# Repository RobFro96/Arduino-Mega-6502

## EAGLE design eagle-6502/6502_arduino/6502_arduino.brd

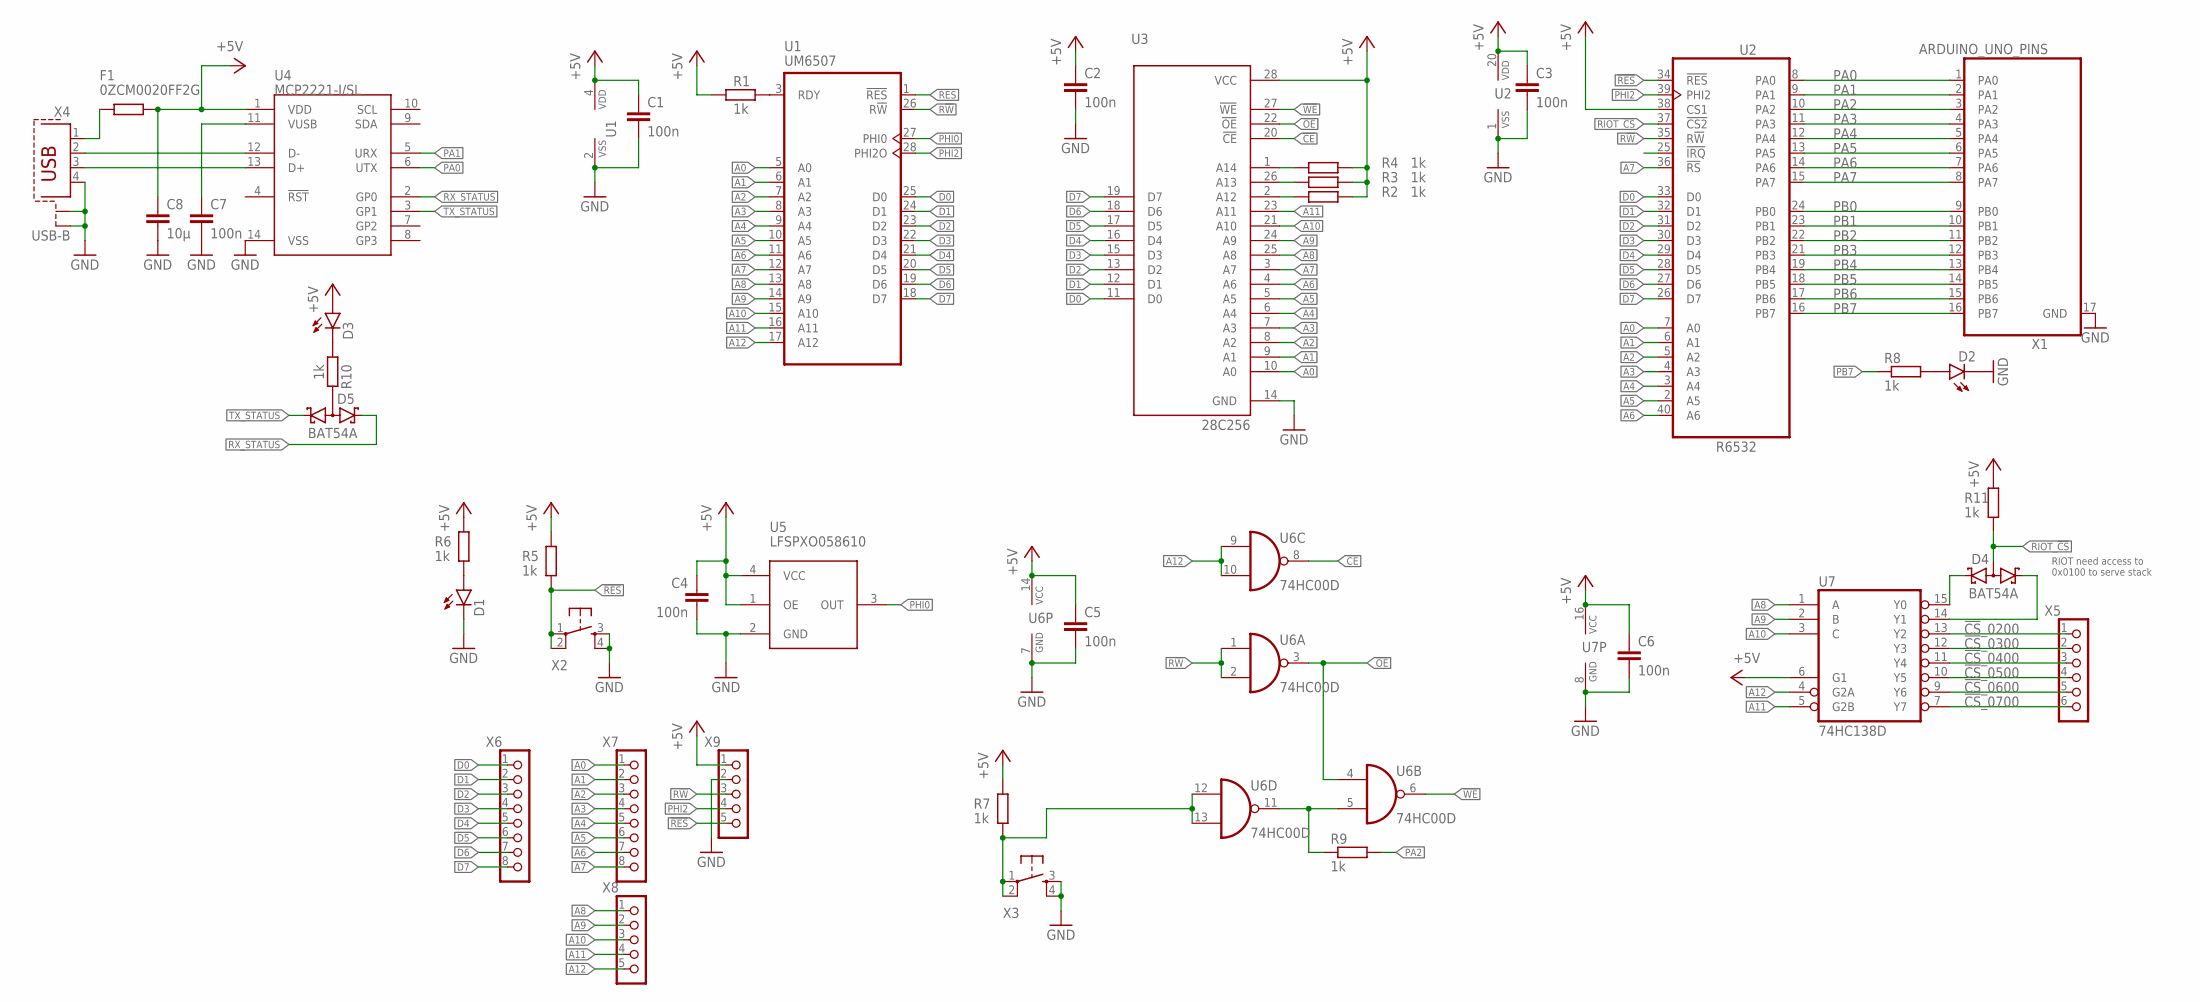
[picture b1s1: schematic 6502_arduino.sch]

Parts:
C1, C2, C3, C4, C5, C6, C7: 100n; C0805
C8: 10µ; C0805
D1, D2, D3: LED; LED3MM
D4, D5: BAT54A; SOT23
F1: 0ZCM0020FF2G; R0603
R1, R2, R3, R4, R5, R6, R7, R8, R9, R10, R11: 1k; R0805
U1: UM6507; DIL28-6
U2: R6532; DIL40
U3: 28C256; DIL28-6
U4: MCP2221-I/SL; SOIC14
U5: LFSPXO058610
U6: 74HC00D; SO14
U7: 74HC138D; SO16
X1: ARDUINO_UNO_PINS; ARDUINO_R3
X2, X3: TACT_SWITCH; TACTILE_SWITCH_PTH_6.0MM
X4: USB-B; PN61729-S
X5: PINHD_6_RND; 1X06
X6, X7: PINHD_8_RND; 1X08
X8, X9: PINHD_5_RND; 1X05

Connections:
!BOOT: R7.1, U6.12 (I0), U6.13 (I1), X3.1, X3.2
!CE: U3.20 (!CE), U6.8 (O)
!CS!_0200: U7.13 (Y2), X5.1
!CS!_0300: U7.12 (Y3), X5.2
!CS!_0400: U7.11 (Y4), X5.3
!CS!_0500: U7.10 (Y5), X5.4
!CS!_0600: U7.9 (Y6), X5.5
!CS!_0700: U7.7 (Y7), X5.6
!OE: U3.22 (!OE), U6.3 (O), U6.4 (I0)
!RES: R5.1, U1.1 (!RES), U2.34 (!RES), X2.1, X2.2, X9.5
!WE: U3.27 (!WE), U6.6 (O)
+5V: C1.1, C2.1, C3.1, C4.1, C5.1, C6.1, C8.1, D3.A, F1.2, R1.1, R2.2, R3.2, R4.2, R5.2, R6.2, R7.2, R11.2, U1.4 (VDD), U2.20 (VDD), U2.38 (CS1), U3.28 (VCC), U4.1 (VDD), U5.1 (OE), U5.4 (VCC), U6.14 (VCC), U7.6 (G1), U7.16 (VCC), X9.1
A0: U1.5 (A0), U2.7 (A0), U3.10 (A0), X7.1
A1: U1.6 (A1), U2.6 (A1), U3.9 (A1), X7.2
A2: U1.7 (A2), U2.5 (A2), U3.8 (A2), X7.3
A3: U1.8 (A3), U2.4 (A3), U3.7 (A3), X7.4
A4: U1.9 (A4), U2.3 (A4), U3.6 (A4), X7.5
A5: U1.10 (A5), U2.2 (A5), U3.5 (A5), X7.6
A6: U1.11 (A6), U2.40 (A6), U3.4 (A6), X7.7
A7: U1.12 (A7), U2.36 (!RS), U3.3 (A7), X7.8
A8: U1.13 (A8), U3.25 (A8), U7.1 (A), X8.1
A9: U1.14 (A9), U3.24 (A9), U7.2 (B), X8.2
A10: U1.15 (A10), U3.21 (A10), U7.3 (C), X8.3
A11: U1.16 (A11), U3.23 (A11), U7.5 (G2B), X8.4
A12: U1.17 (A12), U6.9 (I0), U6.10 (I1), U7.4 (G2A), X8.5
D0: U1.25 (D0), U2.33 (D0), U3.11 (D0), X6.1
D1: U1.24 (D1), U2.32 (D1), U3.12 (D1), X6.2
D2: U1.23 (D2), U2.31 (D2), U3.13 (D2), X6.3
D3: U1.22 (D3), U2.30 (D3), U3.15 (D3), X6.4
D4: U1.21 (D4), U2.29 (D4), U3.16 (D4), X6.5
D5: U1.20 (D5), U2.28 (D5), U3.17 (D5), X6.6
D6: U1.19 (D6), U2.27 (D6), U3.18 (D6), X6.7
D7: U1.18 (D7), U2.26 (D7), U3.19 (D7), X6.8
GND: C1.2, C2.2, C3.2, C4.2, C5.2, C6.2, C7.2, C8.2, D1.K (C), D2.K (C), U1.2 (VSS), U2.1 (VSS), U3.14 (GND), U4.14 (VSS), U5.2 (GND), U6.7 (GND), U7.8 (GND), X1.17 (GND), X2.3, X2.4, X3.3, X3.4, X4.4, X4.S1, X4.S2, X9.2
unnamed: R1.2, U1.3 (RDY)
unnamed: D1.A, R6.1
unnamed: R9.1, U6.5 (I1), U6.11 (O)
unnamed: D2.A, R8.2
unnamed: U4.12 (D-), X4.2
unnamed: U4.13 (D+), X4.3
unnamed: D3.K (C), R10.1
unnamed: C7.1, U4.11 (VUSB)
unnamed: D5.3 (AA), R10.2
unnamed: F1.1, X4.1
unnamed: D4.1 (K1), U7.15 (Y0)
unnamed: R2.1, U3.2 (A12)
unnamed: R3.1, U3.26 (A13)
unnamed: R4.1, U3.1 (A14)
unnamed: D4.2 (K2), U7.14 (Y1)
PA0: U2.8 (PA0), U4.6 (UTX), X1.1 (PA0)
PA1: U2.9 (PA1), U4.5 (URX), X1.2 (PA1)
PA2: R9.2, U2.10 (PA2), X1.3 (PA2)
PA3: U2.11 (PA3), X1.4 (PA3)
PA4: U2.12 (PA4), X1.5 (PA4)
PA5: U2.13 (PA5), X1.6 (PA5)
PA6: U2.14 (PA6), X1.7 (PA6)
PA7: U2.15 (PA7), X1.8 (PA7)
PB0: U2.24 (PB0), X1.9 (PB0)
PB1: U2.23 (PB1), X1.10 (PB1)
PB2: U2.22 (PB2), X1.11 (PB2)
PB3: U2.21 (PB3), X1.12 (PB3)
PB4: U2.19 (PB4), X1.13 (PB4)
PB5: U2.18 (PB5), X1.14 (PB5)
PB6: U2.17 (PB6), X1.15 (PB6)
PB7: R8.1, U2.16 (PB7), X1.16 (PB7)
PHI0: U1.27 (PHI0), U5.3 (OUT)
PHI2: U1.28 (PHI2O), U2.39 (PHI2), X9.4
R!W: U1.26 (R!W), U2.35 (R!W), U6.1 (I0), U6.2 (I1), X9.3
RIOT_!CS: D4.3 (AA), R11.1, U2.37 (!CS2)
RX_STATUS: D5.2 (K2), U4.2 (GP0)
TX_STATUS: D5.1 (K1), U4.3 (GP1)

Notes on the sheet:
RIOT need access to 0x0100 to serve stack

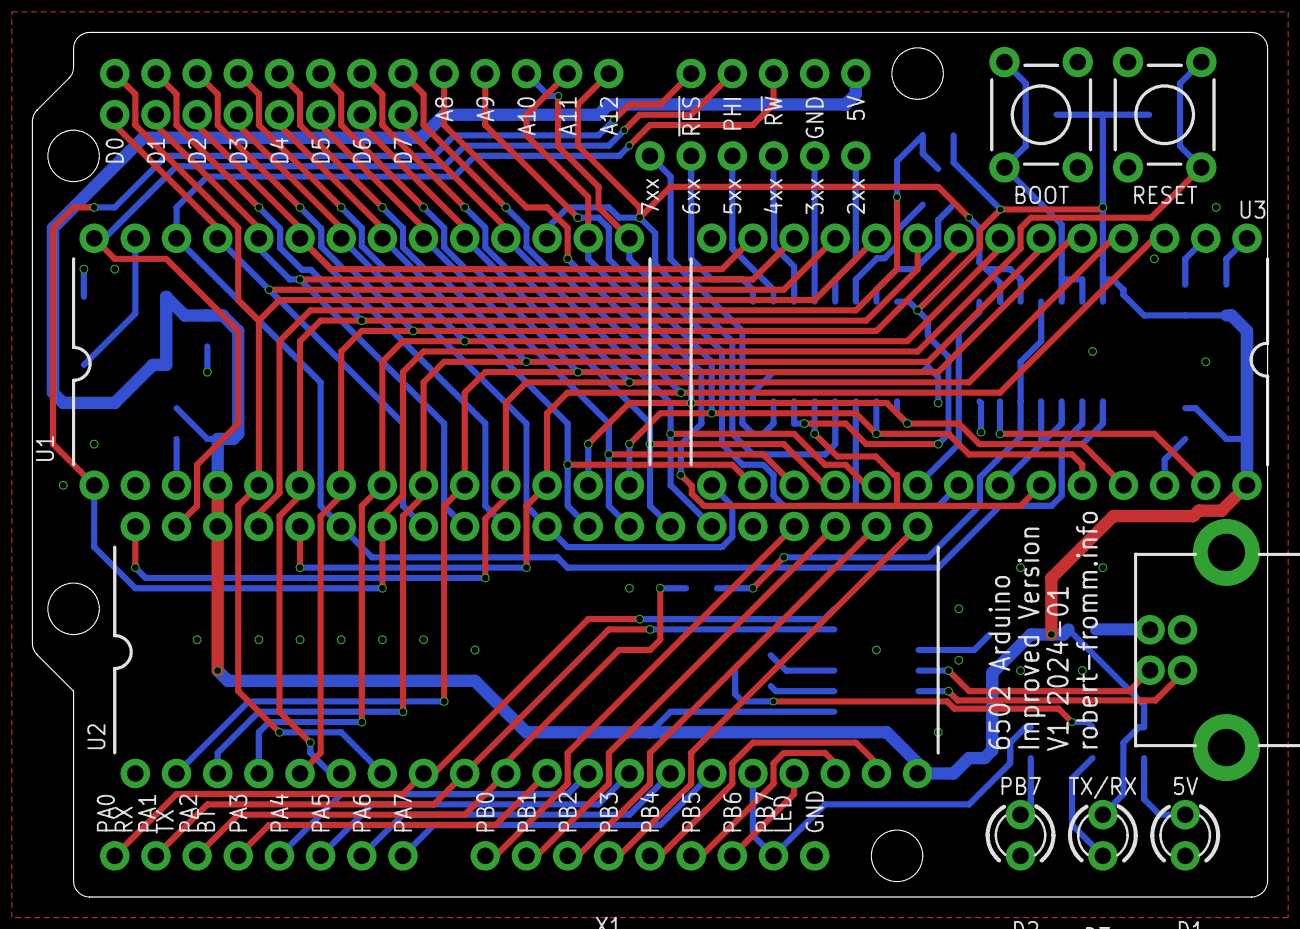
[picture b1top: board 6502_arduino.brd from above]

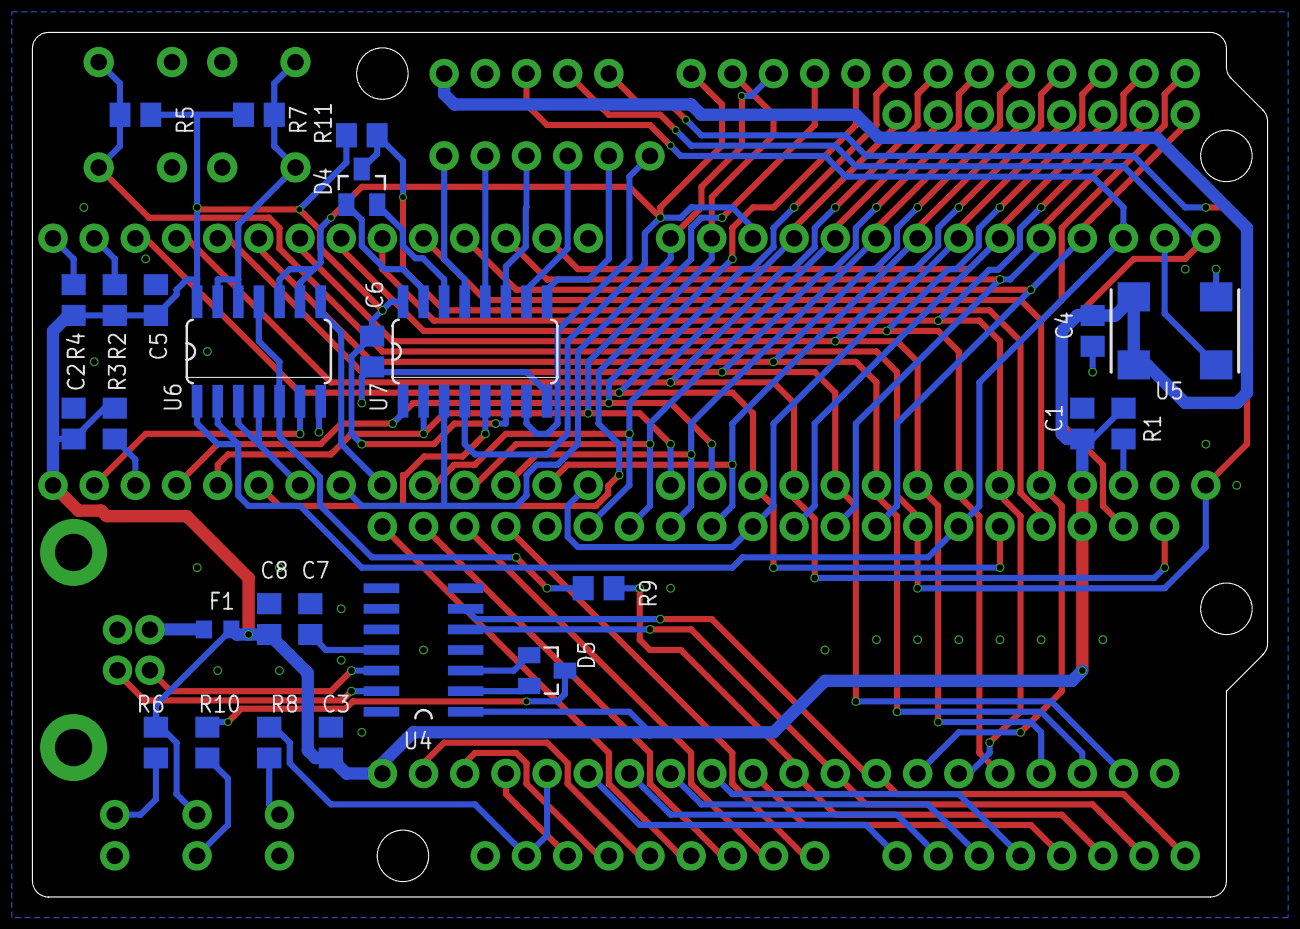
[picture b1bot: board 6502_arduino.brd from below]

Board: 2 copper layers, 76.2 x 53.3 mm, 41 parts (26 on the bottom side), 71 nets.

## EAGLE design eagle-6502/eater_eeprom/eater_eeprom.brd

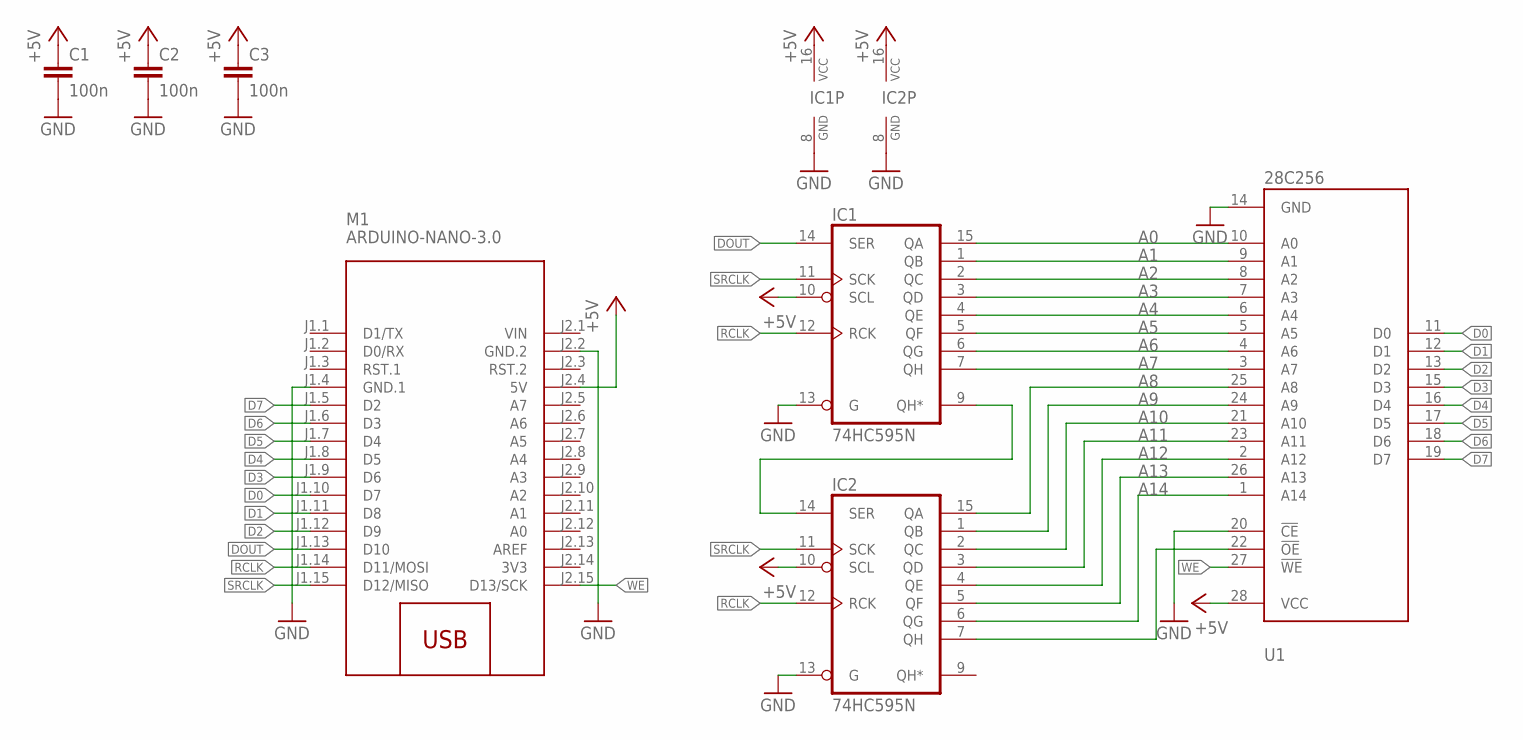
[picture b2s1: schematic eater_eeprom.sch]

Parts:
C1, C2, C3: 100n; C0805
IC1, IC2: 74HC595N; DIL16
M1: ARDUINO-NANO-3.0
U1: 28C256; DIL28-6

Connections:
3V3: M1.J2.14 (3V3)
+5V: C1.1, C2.1, C3.1, IC1.10 (SCL), IC1.16 (VCC), IC2.10 (SCL), IC2.16 (VCC), M1.J2.4 (5V), U1.28 (VCC)
A0: IC1.15 (QA), U1.10 (A0)
A1: IC1.1 (QB), U1.9 (A1)
A2: IC1.2 (QC), U1.8 (A2)
A3: IC1.3 (QD), U1.7 (A3)
A4: IC1.4 (QE), U1.6 (A4)
A5: IC1.5 (QF), U1.5 (A5)
A6: IC1.6 (QG), U1.4 (A6)
A7: IC1.7 (QH), U1.3 (A7)
A8: IC2.15 (QA), U1.25 (A8)
A9: IC2.1 (QB), U1.24 (A9)
A10: IC2.2 (QC), U1.21 (A10)
A11: IC2.3 (QD), U1.23 (A11)
A12: IC2.4 (QE), U1.2 (A12)
A13: IC2.5 (QF), U1.26 (A13)
A14: IC2.6 (QG), U1.1 (A14)
D0: M1.J1.10 (D7), U1.11 (D0)
D1: M1.J1.11 (D8), U1.12 (D1)
D2: M1.J1.12 (D9), U1.13 (D2)
D3: M1.J1.9 (D6), U1.15 (D3)
D4: M1.J1.8 (D5), U1.16 (D4)
D5: M1.J1.7 (D4), U1.17 (D5)
D6: M1.J1.6 (D3), U1.18 (D6)
D7: M1.J1.5 (D2), U1.19 (D7)
DOUT: IC1.14 (SER), M1.J1.13 (D10)
GND: C1.2, C2.2, C3.2, IC1.8 (GND), IC1.13 (G), IC2.8 (GND), IC2.13 (G), M1.J1.4 (GND.1), M1.J2.2 (GND.2), U1.14 (GND), U1.20 (!CE)
unnamed: IC1.9 (QH*), IC2.14 (SER)
unnamed: IC2.7 (QH), U1.22 (!OE)
RCLK: IC1.12 (RCK), IC2.12 (RCK), M1.J1.14 (D11/MOSI)
SRCLK: IC1.11 (SCK), IC2.11 (SCK), M1.J1.15 (D12/MISO)
VIN: M1.J2.1 (VIN)
WE: M1.J2.15 (D13/SCK), U1.27 (!WE)

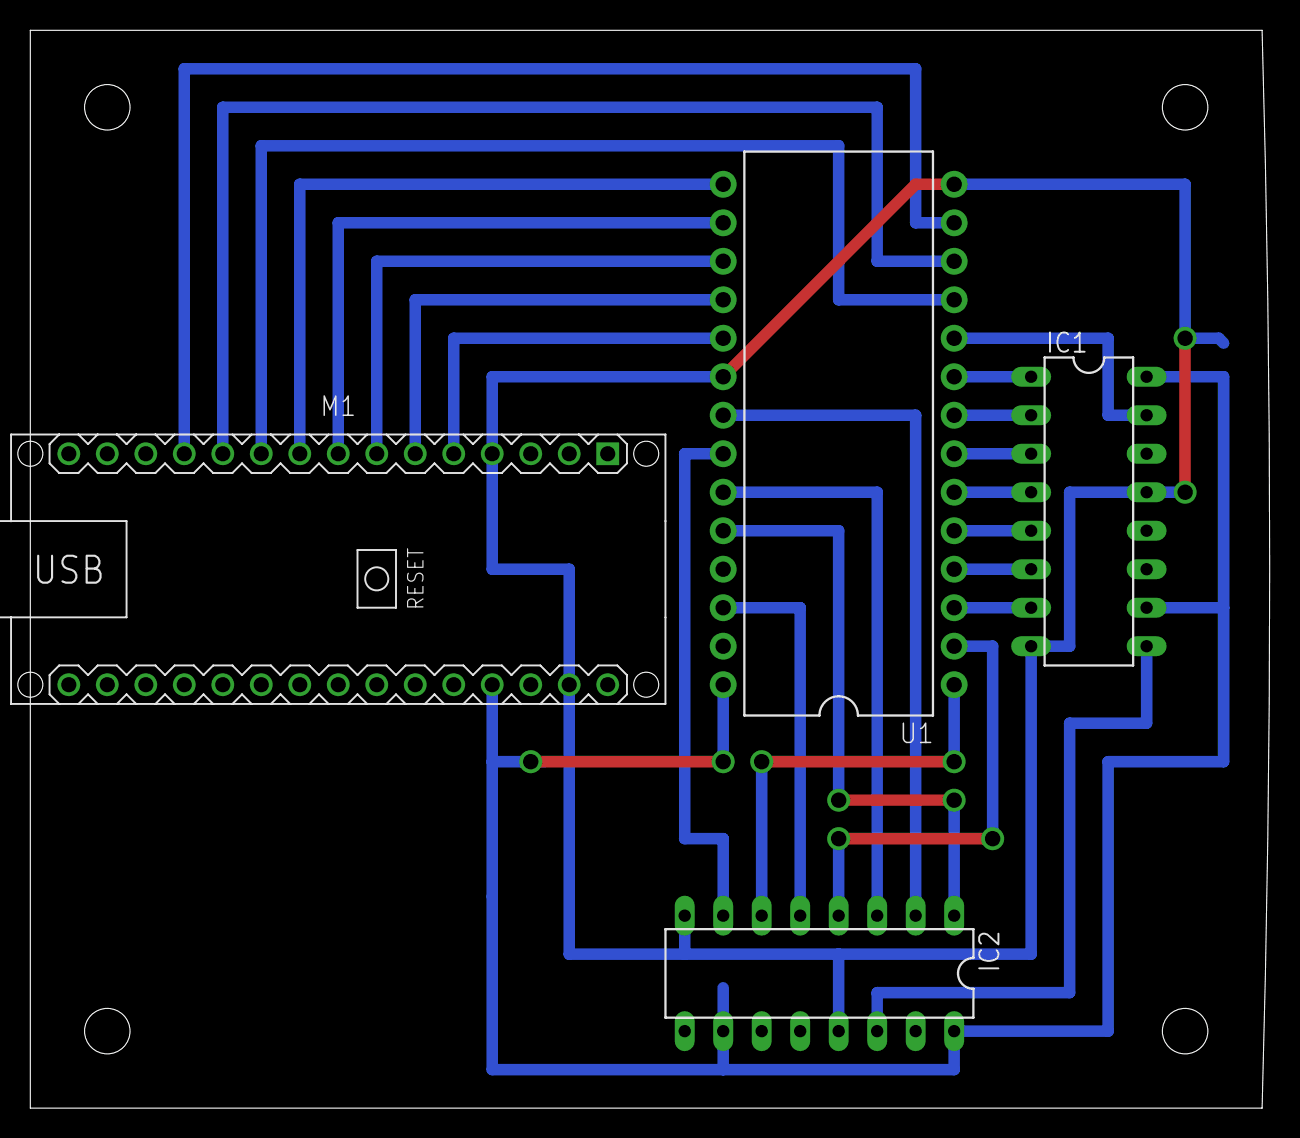
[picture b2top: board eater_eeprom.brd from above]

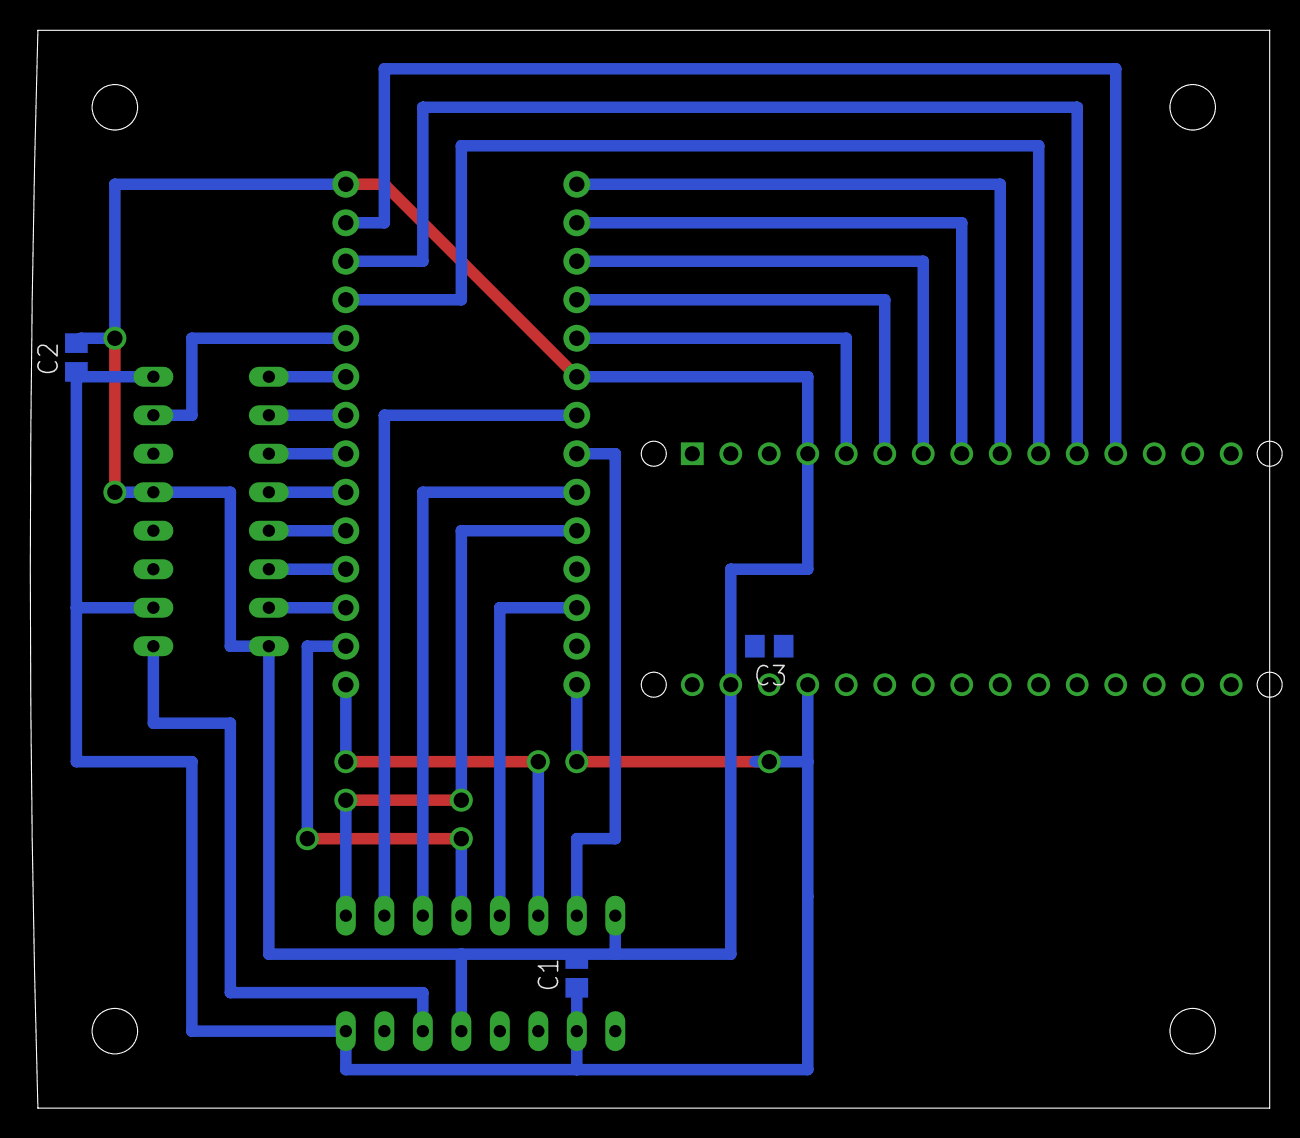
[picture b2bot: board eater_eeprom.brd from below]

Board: 2 copper layers, 81.8 x 71.1 mm, 7 parts (3 on the bottom side), 31 nets.

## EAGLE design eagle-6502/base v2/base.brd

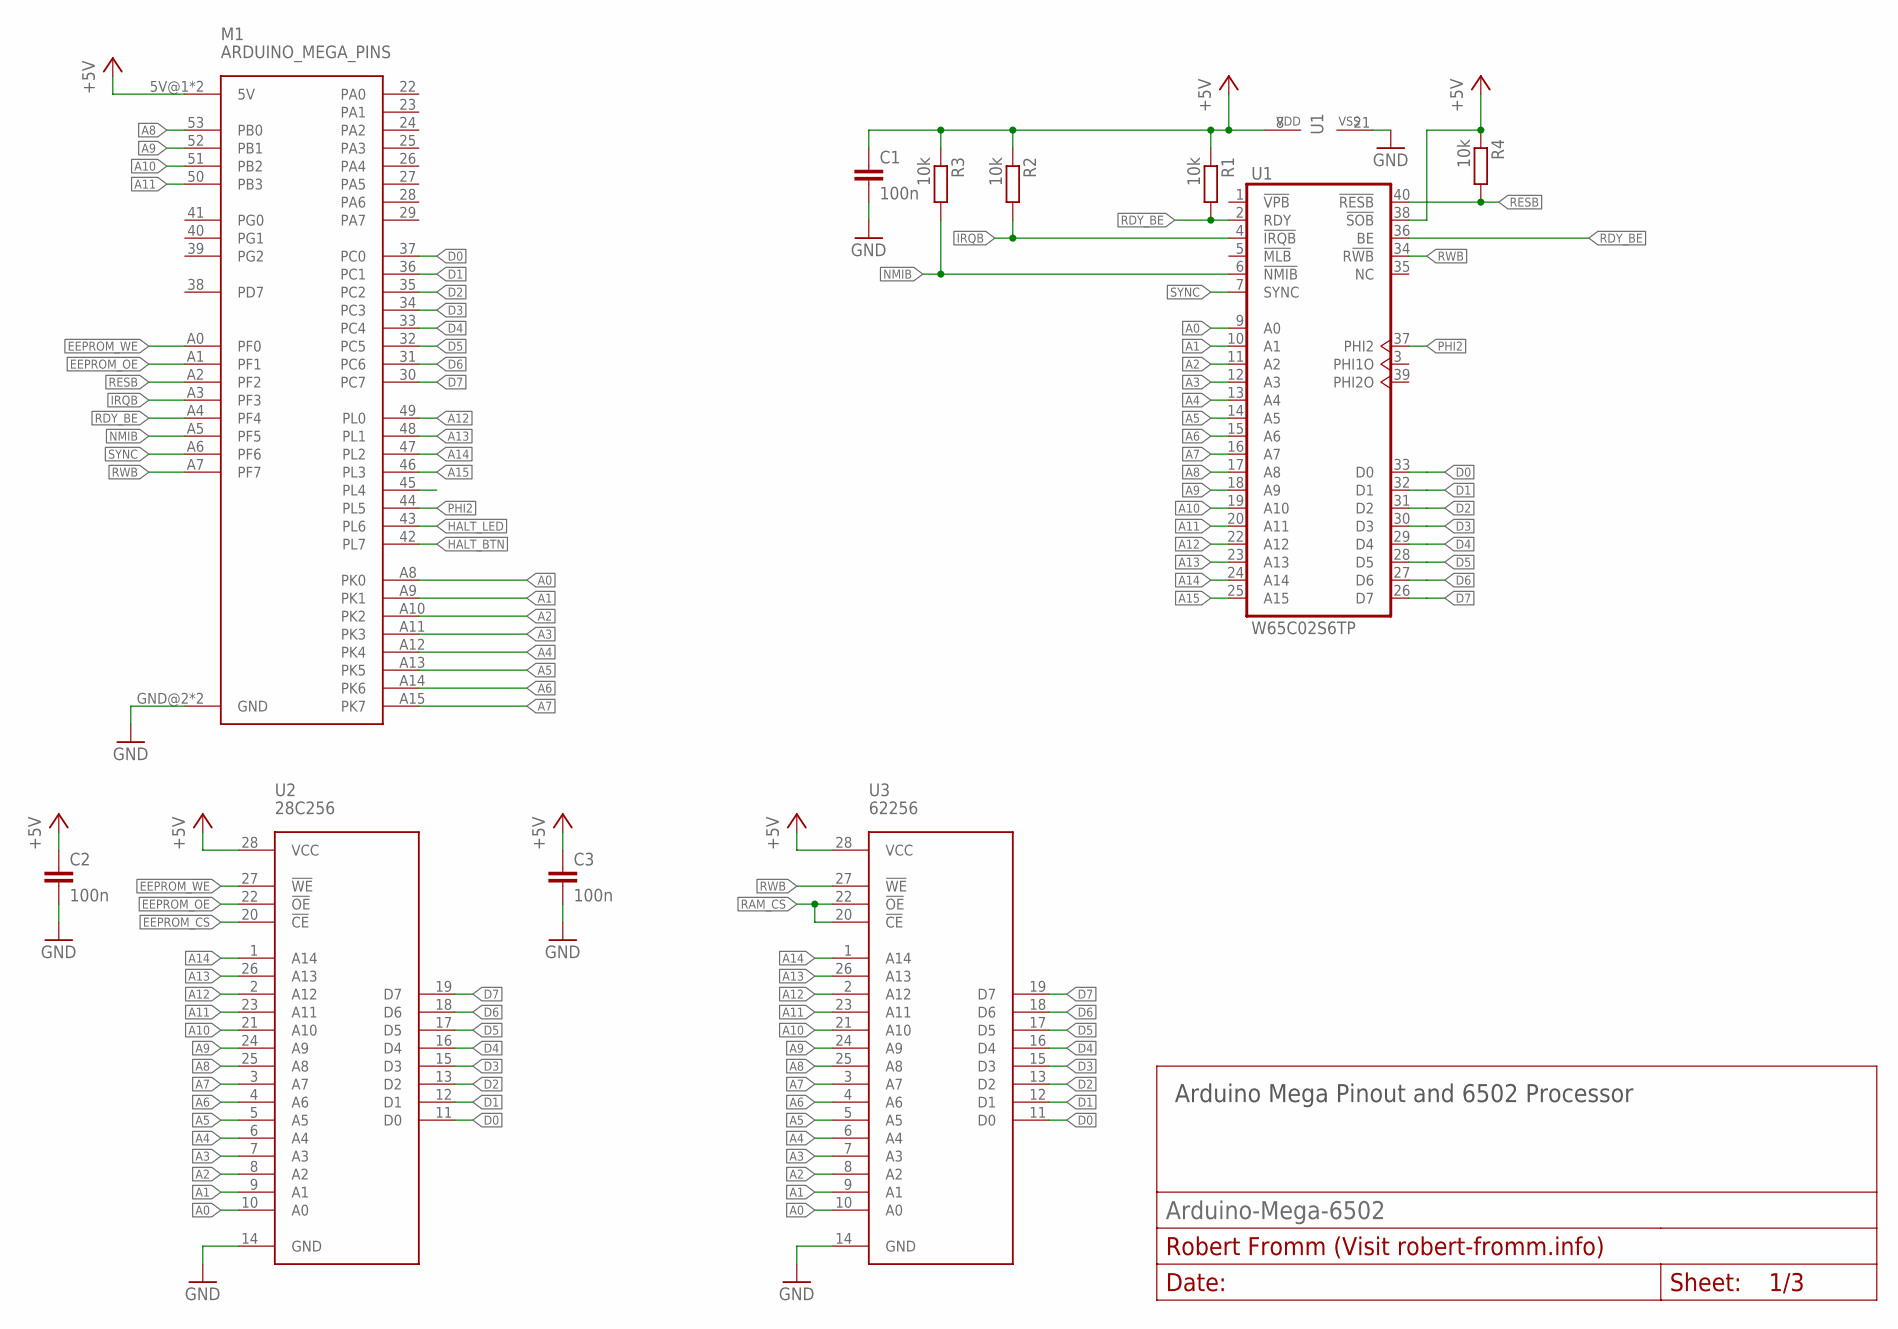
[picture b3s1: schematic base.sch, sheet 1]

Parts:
C1, C2, C3: 100n; C0805
M1: ARDUINO_MEGA_PINS
R1, R2, R3, R4: 10k; R0805
U1: W65C02S6TP; DIL40
U2: 28C256; DIL28-6
U3: 62256; DIL28-6

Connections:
+5V: C1.1, C2.1, C3.1, M1.5V@1 (5V), M1.5V@2 (5V), R1.1, R2.1, R3.1, R4.1, U1.8 (VDD), U1.38 (!SOB), U2.28 (VCC), U3.28 (VCC); also elsewhere on the board
A0: M1.A8 (PK0), U1.9 (A0), U2.10 (A0), U3.10 (A0); also elsewhere on the board
A1: M1.A9 (PK1), U1.10 (A1), U2.9 (A1), U3.9 (A1); also elsewhere on the board
A2: M1.A10 (PK2), U1.11 (A2), U2.8 (A2), U3.8 (A2); also elsewhere on the board
A3: M1.A11 (PK3), U1.12 (A3), U2.7 (A3), U3.7 (A3); also elsewhere on the board
A4: M1.A12 (PK4), U1.13 (A4), U2.6 (A4), U3.6 (A4); also elsewhere on the board
A5: M1.A13 (PK5), U1.14 (A5), U2.5 (A5), U3.5 (A5); also elsewhere on the board
A6: M1.A14 (PK6), U1.15 (A6), U2.4 (A6), U3.4 (A6); also elsewhere on the board
A7: M1.A15 (PK7), U1.16 (A7), U2.3 (A7), U3.3 (A7); also elsewhere on the board
A8: M1.53 (PB0), U1.17 (A8), U2.25 (A8), U3.25 (A8); also elsewhere on the board
A9: M1.52 (PB1), U1.18 (A9), U2.24 (A9), U3.24 (A9); also elsewhere on the board
A10: M1.51 (PB2), U1.19 (A10), U2.21 (A10), U3.21 (A10); also elsewhere on the board
A11: M1.50 (PB3), U1.20 (A11), U2.23 (A11), U3.23 (A11); also elsewhere on the board
A12: M1.49 (PL0), U1.22 (A12), U2.2 (A12), U3.2 (A12); also elsewhere on the board
A13: M1.48 (PL1), U1.23 (A13), U2.26 (A13), U3.26 (A13); also elsewhere on the board
A14: M1.47 (PL2), U1.24 (A14), U2.1 (A14), U3.1 (A14); also elsewhere on the board
A15: M1.46 (PL3), U1.25 (A15); also elsewhere on the board
D0: M1.37 (PC0), U1.33 (D0), U2.11 (D0), U3.11 (D0); also elsewhere on the board
D1: M1.36 (PC1), U1.32 (D1), U2.12 (D1), U3.12 (D1); also elsewhere on the board
D2: M1.35 (PC2), U1.31 (D2), U2.13 (D2), U3.13 (D2); also elsewhere on the board
D3: M1.34 (PC3), U1.30 (D3), U2.15 (D3), U3.15 (D3); also elsewhere on the board
D4: M1.33 (PC4), U1.29 (D4), U2.16 (D4), U3.16 (D4); also elsewhere on the board
D5: M1.32 (PC5), U1.28 (D5), U2.17 (D5), U3.17 (D5); also elsewhere on the board
D6: M1.31 (PC6), U1.27 (D6), U2.18 (D6), U3.18 (D6); also elsewhere on the board
D7: M1.30 (PC7), U1.26 (D7), U2.19 (D7), U3.19 (D7); also elsewhere on the board
EEPROM_!CS: U2.20 (!CE); also elsewhere on the board
EEPROM_!OE: M1.A1 (PF1), U2.22 (!OE)
EEPROM_!WE: M1.A0 (PF0), U2.27 (!WE)
GND: C1.2, C2.2, C3.2, M1.GND@2 (GND), M1.GND@3 (GND), U1.21 (VSS), U2.14 (GND), U3.14 (GND); also elsewhere on the board
HALT_BTN: M1.42 (PL7); also elsewhere on the board
HALT_LED: M1.43 (PL6); also elsewhere on the board
IRQB: M1.A3 (PF3), R2.2, U1.4 (!IRQB); also elsewhere on the board
NMIB: M1.A5 (PF5), R3.2, U1.6 (!NMIB); also elsewhere on the board
PHI2: M1.44 (PL5), U1.37 (PHI2); also elsewhere on the board
RAM_!CS: U3.20 (!CE), U3.22 (!OE); also elsewhere on the board
RDY_BE: M1.A4 (PF4), R1.2, U1.2 (RDY), U1.36 (BE)
RESB: M1.A2 (PF2), R4.2, U1.40 (!RESB); also elsewhere on the board
RWB: M1.A7 (PF7), U1.34 (R!WB), U3.27 (!WE); also elsewhere on the board
SYNC: M1.A6 (PF6), U1.7 (SYNC); also elsewhere on the board

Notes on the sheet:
Arduino Mega Pinout and 6502 Processor

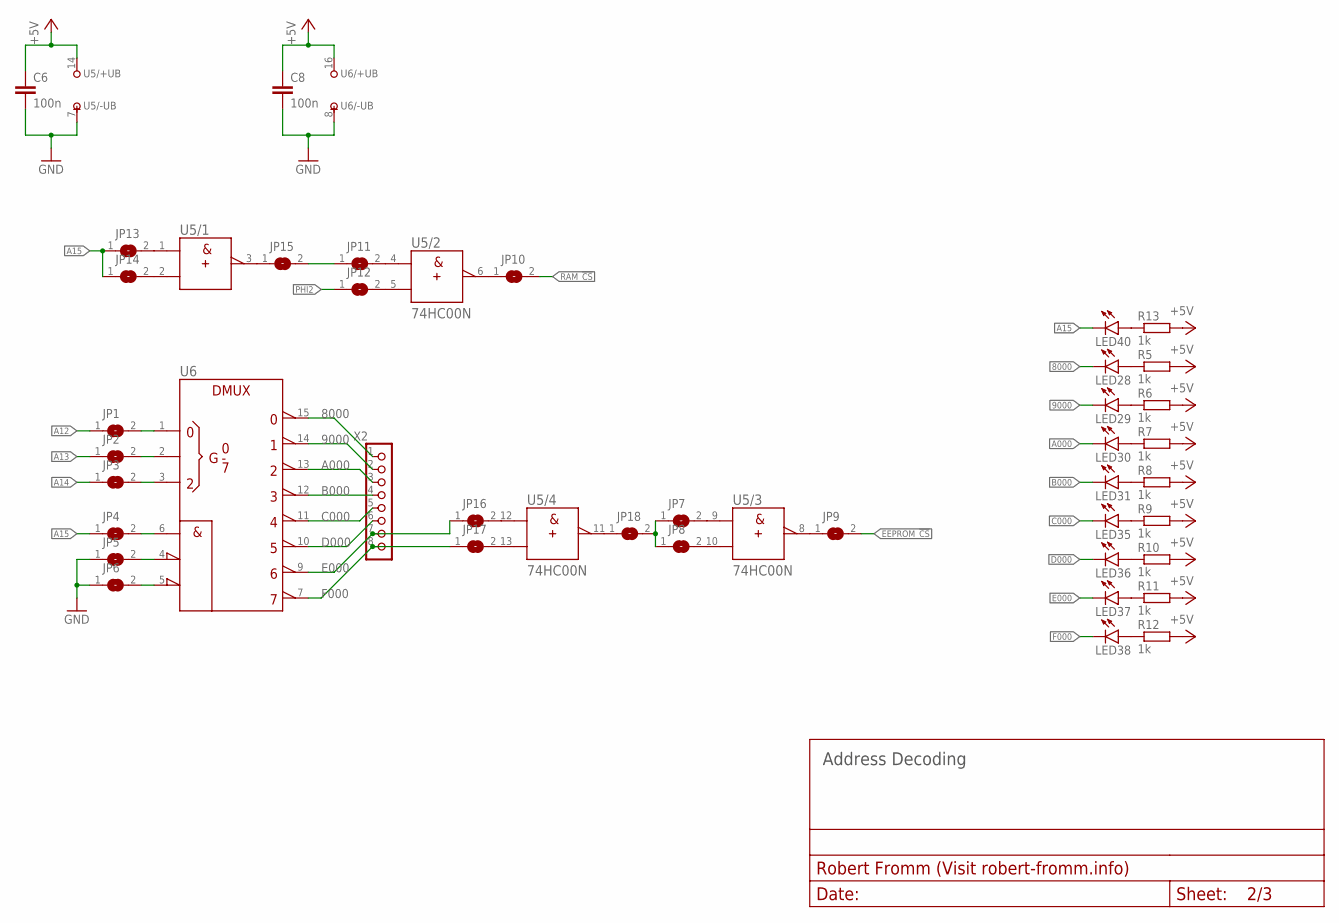
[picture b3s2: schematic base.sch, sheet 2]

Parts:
C6, C8: 100n; C0805
JP1, JP2, JP3, JP4, JP5, JP6, JP7, JP8, JP9, JP10, JP11, JP12, JP13, JP14, JP15, JP16, JP17, JP18: SJ
LED28, LED29, LED30, LED31, LED35, LED36, LED37, LED38, LED40: LEDSML0805; SML0805
R5, R6, R7, R8, R9, R10, R11, R12, R13: 1k; R0805
U5: 74HC00N; DIL14
U6: 74138N; DIL16
X2: PINHD_8_RND; 1X08

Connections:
8000: LED28.C, U6.15 (Y0), X2.1
9000: LED29.C, U6.14 (Y1), X2.2
+5V: C6.1, C8.1, R5.2, R6.2, R7.2, R8.2, R9.2, R10.2, R11.2, R12.2, R13.2, U5.14 (+UB), U6.16 (+UB); also elsewhere on the board
A000: LED30.C, U6.13 (Y2), X2.3
A12: JP1.1; also elsewhere on the board
A13: JP2.1; also elsewhere on the board
A14: JP3.1; also elsewhere on the board
A15: JP4.1, JP13.1, JP14.1, LED40.C; also elsewhere on the board
B000: LED31.C, U6.12 (Y3), X2.4
C000: LED35.C, U6.11 (Y4), X2.5
D000: LED36.C, U6.10 (Y5), X2.6
E000: JP16.1, LED37.C, U6.9 (Y6), X2.7
EEPROM_!CS: JP9.2; also elsewhere on the board
F000: JP17.1, LED38.C, U6.7 (Y7), X2.8
GND: C6.2, C8.2, JP5.1, JP6.1, U5.7 (-UB), U6.8 (-UB); also elsewhere on the board
unnamed: LED40.A, R13.1
unnamed: JP7.2, U5.9 (A)
unnamed: JP8.2, U5.10 (B)
unnamed: JP9.1, U5.8 (Y)
unnamed: JP1.2, U6.1 (A)
unnamed: JP2.2, U6.2 (B)
unnamed: JP3.2, U6.3 (C)
unnamed: JP5.2, U6.4 (!G2A)
unnamed: JP6.2, U6.5 (!G2B)
unnamed: JP4.2, U6.6 (G1)
unnamed: JP17.2, U5.13 (B)
unnamed: JP10.1, U5.6 (Y)
unnamed: JP13.2, U5.1 (A)
unnamed: JP14.2, U5.2 (B)
unnamed: JP15.1, U5.3 (Y)
unnamed: JP18.1, U5.11 (Y)
unnamed: JP11.1, JP15.2
unnamed: JP16.2, U5.12 (A)
unnamed: JP7.1, JP8.1, JP18.2
unnamed: JP11.2, U5.4 (A)
unnamed: JP12.2, U5.5 (B)
unnamed: LED28.A, R5.1
unnamed: LED29.A, R6.1
unnamed: LED30.A, R7.1
unnamed: LED31.A, R8.1
unnamed: LED35.A, R9.1
unnamed: LED36.A, R10.1
unnamed: LED37.A, R11.1
unnamed: LED38.A, R12.1
PHI2: JP12.1; also elsewhere on the board
RAM_!CS: JP10.2; also elsewhere on the board

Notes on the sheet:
Address Decoding

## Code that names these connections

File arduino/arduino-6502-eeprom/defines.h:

const uint8_t PROTOCOL_START_BYTE = 0xFF;     //!> Value of the start byte
const uint8_t PROTOCOL_MESSAGE_EXTRA_LEN = 3; //!> Length of the total message = PROTOCOL_MESSAGE_EXTRA_LEN + Payload Length
const uint8_t PROTOCOL_COMMAND = 1;           //!> Index of the command byte
const uint8_t PROTOCOL_PAYLOAD_LEN = 2;       //!> Index of the payload length
const uint8_t PROTOCOL_DATA = 3;              //!> Index of the first data byte

const uint8_t PROTOCOL_WHOIAM_VALUE = 0xf2;
const uint8_t PROTOCOL_VERSION = 1;

const uint8_t CMD_API_ACTION_SINGLE_STEP = (1 << 0);
const uint8_t CMD_API_ACTION_RUN = (1 << 1);
const uint8_t CMD_API_ACTION_RESET = (1 << 2);
const uint8_t CMD_API_ACTION_NMI = (1 << 3);
const uint8_t CMD_API_ACTION_IRQ = (1 << 4);
const uint8_t CMD_API_ACTION_AUTO_RESET = (1 << 5);

typedef enum
{
    CMD_WHOIAM_VERSION = 1,
    CMD_MEM_REQUEST = 2,
    CMD_MEM_WRITE = 3,
    CMD_MEM_PAGE_WRITE = 4,
    CMD_BUS_ACTION = 5,
    CMD_API_ACTIONS = 6
} protocol_cmd_t;

// Control Bus PORTK
const uint8_t RDY_BE = (1 << 1);
const uint8_t RESB = (1 << 2);
const uint8_t PHI2 = (1 << 3);
const uint8_t RWB = (1 << 4);
const uint8_t IRQB = (1 << 5);
const uint8_t NMIB = (1 << 6);
const uint8_t SYNC = (1 << 7);

// Auxillary PORTG
const uint8_t HALT_LED = (1 << 0);
const uint8_t HALT_BTN = (1 << 1);
const uint8_t EEPROM_WE = (1 << 2);

// Auxiallary PORTD
const uint8_t EEPROM_OE = (1 << 7);

#define p_abus_val_l() (PINL)
#define p_abus_val_h() (PINC)

uint16_t p_abus_val()
{
    return (uint16_t)p_abus_val_l() + (((uint16_t)p_abus_val_h()) << 8);
}
#define p_abus_output() ({ DDRL = 0xFF; DDRC=0xFF; })
#define p_abus_input() ({ DDRL = 0x00; DDRC = 0x00; })
void p_abus_set(uint16_t abus)
{
    PORTL = abus;
    PORTC = abus >> 8;
}

#define p_dbus_val() (PINA)
#define p_dbus_output() ({ DDRA = 0xFF; })
#define p_dbus_input() ({ DDRA = 0x00; })
void p_dbus_set(uint8_t dbus)
{
    PORTA = dbus;
}

#define p_cbus_val() (PINK)
uint8_t p_cbus_vectors_set(uint8_t cbus)
{
    const uint8_t allowed_pulldown = IRQB + NMIB + RESB;
    DDRK = (cbus & allowed_pulldown) + (DDRK & ~allowed_pulldown);
}

#define p_reset_l() ({ DDRK |= RESB; })
#define p_reset_h() ({ DDRK &= ~RESB; })
#define p_reset_val() (PINK & RESB)

#define p_irq_l() ({ DDRK |= IRQB; })
#define p_nmi_l() ({ DDRK |= NMIB; })

#define p_phi2_l() ({ PORTK &= ~PHI2; })
#define p_phi2_h() ({ PORTK |= PHI2; })

#define p_rdy_be_l() ({ DDRK |= RDY_BE; })
#define p_rdy_be_h() ({ DDRK &= ~RDY_BE; })

#define p_eeprom_we_l() ({ PORTG &= ~EEPROM_WE; })
#define p_eeprom_we_h() ({ PORTG |= EEPROM_WE; })

#define p_eeprom_oe_l() ({ PORTD &= ~EEPROM_OE; })
#define p_eeprom_oe_h() ({ PORTD |= EEPROM_OE; })

void p_halt_led_set(uint8_t state)
{
    if (state)
        PORTG |= HALT_LED;
    else
        PORTG &= ~HALT_LED;
}

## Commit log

2021-02-06 In-Cicruit EEPROM Programmer: Arduino Program
2021-02-06 In Progress: 6502-Terminal
2021-02-06 Removed IDE
2021-02-07 Terminal Feature Complete
2021-02-07 Added example programs
2021-02-10 Added comments to program
2021-03-14 Updated Schematic, Added PDF
2021-03-14 Updated Schematic PDF
2021-03-22 Update binary file before transmission
2021-03-22 Updated Examples
2021-11-27 Update Examples
2021-11-28 Apple I Replica, Memory Map, Virtual IO, Examples
2023-12-06 Added Eagle Version 2 hardware design
2023-12-06 updates misc files
2023-12-07 Added RIOT+6507 test files
2023-12-07 Added EEPROM programmer (see Ben Eater)
2023-12-08 EEPROM Programmer working over UART
2023-12-09 Moved 6507 RIOT programs
2023-12-09 Added Assembler and Programm Python CLI
2024-01-01 Porting WozMon to work with software UART
2024-01-03 Added wozmon code output to asmandprog and an example
2024-01-03 programming EEPROM over WozMon
2024-01-03 Removed assembled .bin files
2024-01-03 added .bin to gitignore
2024-01-03 Updated vasm, creating and reading listing file to output labels
2024-01-04 added flag to asmandprog to delete temp.lst
2024-01-04 Added unused vasm files
2024-01-04 Modding WozMon to write to EEPROM -> robfro_wozmon.asm
2024-01-04 Change wozmon to use local labels asmandprog to output label with = symbol
2024-01-05 Added write protect jumper and automatic program selection
2024-01-05 Added UART_CONF to configure UART: upper case only, disable echo, only output important echos
2024-01-05 Reconfigured write protect as boot button
2024-01-10 First version of 6502 Arduino PCB
2024-01-12 Tested PCB design on breadboard, added BAT54A ORing on 74x138 lines to allow stack served by RIOT, ORing of UART status LEDs
2024-02-25 Populated and tested PCB. Added fixes in robfro_wozmon and Errata list of PCB errors

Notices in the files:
parts and their libraries:
SparkFun-Aesthetics: Licensing: Creative Commons ShareAlike 4.0 International - https://creativecommons.org/licenses/by-sa/4.0
diy-modules: Released under the Creative Commons Attribution 4.0 International License: http://creativecommons.org/licenses/by/4.0
